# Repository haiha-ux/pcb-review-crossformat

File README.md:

# Reviewing Altium / Eagle (and other) PCB designs in KiCad: how faithful is the import?

Clients send board files from Altium, Eagle, EasyEDA or Allegro. Before reviewing such a file in KiCad 10, I want
to know what the import keeps and what it silently changes. This repo measures that on two public boards, then (next
milestone) reviews each one the way a client would get it.

**Status:** milestone 1 (import fidelity) done; milestone 2 adds one sample review report per board
(`review/*/REVIEW.md`).

## The two sample boards

| | Altium | Eagle |
|---|---|---|
| Board | Bluetooth audio receiver (JieLi IC), 50 × 43 mm, 2 layers | SparkFun Qwiic Button, 25.4 × 25.4 mm, 2 layers, and its 3 × 3 production panel |
| Source | github.com/LZH-ang/Bluetooth-Audio-with-JieLi-IC, `PCB_Project/` | github.com/sparkfun/Qwiic_Button, `Hardware/`, `Production/` |
| License | GPL-3.0 (`samples/altium_blv/original/LICENSE`) | CC BY-SA 4.0 (`samples/eagle_qwiic_button/original/LICENSE.md`) |
| Design file | `BLV.PcbDoc` (native binary, OLE), `BLV.SchDoc` | `Qwiic_Button.brd` / `.sch` (Eagle 9.5.2 XML), `Qwiic_Button-Panel.brd` |
| Maker's Gerbers | `BLV.GTL/GBL/GTS/GBS/GTO/GBO/GKO`, NC drill, drill report | `Qwiic_Button-Panel.GTL/…/GKO`, Excellon `.TXT` |

The sample files are copied unchanged under `samples/*/original/`, with their licenses. Everything else in this
repo is my own work.

I chose a native binary PcbDoc on purpose. Many "Altium" files on GitHub are the ASCII variant exported by EasyEDA
(they start with `|RECORD=`), and those exercise a different reader.

## Method

1. **Import:** `kicad-cli pcb import --format altium|eagle` (KiCad 10.0.8), saved with its JSON import report
   (`samples/*/kicad/import_report*.json`).
2. **"Before" numbers from the original file, without KiCad** (`tools/source_metrics.py`).
   - PcbDoc: each `<Name>6/Header` stream holds the record count of `<Name>6/Data`. `Tracks6` is decoded record by
     record, with the layout from KiCad's `altium_parser_pcb.cpp`, so free copper tracks can be told apart from
     polygon and footprint primitives.
   - Eagle: the XML is read directly.
   - Rules: read from the PcbDoc `Rules6` stream and the Eagle `<designrules>`.
3. **"After" numbers from KiCad** (`tools/kicad_metrics.py`, pcbnew).
4. **Copper check against the maker's Gerbers** (`tools/reexport.py`, `tools/gerber_xor.py`).
   - The design is loaded through KiCad's importer, zones are refilled, and Gerbers and drill files are written.
   - Each layer is then drawn by gerbonara (an independent Gerber reader), rasterised at 0.05 mm/pixel and XORed
     against the maker's Gerber.
   - The two sets are registered on the top copper by phase correlation, because they do not share an origin and
     their outline layers differ.
   - Differences thinner than about 0.15 mm (3 pixels) are treated as rasterisation noise.
   - Tool check: the same file against itself gives 0.000 mm². F.Cu against B.Cu of one board gives 52 / 194 mm².

## Fidelity: Altium `BLV.PcbDoc`

| Item | Original (PcbDoc) | After KiCad import | Verdict |
|---|---|---|---|
| Components / footprints | 33 | 36 | The 3 extras are the free pads of the three 3.048 mm holes, wrapped in unnamed footprints |
| Nets | 31 | 31 | same |
| Pads | 109 | 110 (97 SMD, 13 PTH) | +1 is the printed antenna of A3: copper inside the footprint that carries a net, which KiCad can only keep as a pad, so it becomes a 17.5 × 6.35 mm custom-shape pad next to the real feed pad |
| Vias | 102 | 102 | same |
| Free copper tracks (straight, `Tracks6`) | 81 | 81 | same |
| Free copper arcs (`Arcs6`) | 51 | 50 | the missing arc is 0.0002 mm long (a 0.012° sweep at net 25); KiCad drops it as degenerate |
| Straight track length, top / bottom | 118.99 / 59.56 mm | 118.99 / 59.56 mm | identical to 0.01 mm |
| Arc length, top / bottom | 48.78 / 10.50 mm | 48.78 / 10.50 mm | identical |
| **All free copper (tracks + arcs), top / bottom** | **167.77 / 70.06 mm** | **167.77 / 70.06 mm** | identical |
| Polygons | 6 | 6 zones | same; each keeps its 10 mil gap |
| Keep-out tracks | 3 | 3 rule areas | kept as keep-outs |
| Drill hits | 115 (BLV.DRR) | 115 | same |
| Clearance rule | 10 mil | 0.2 mm default (7.9 mil) | **lost** |
| Track width rule | min 10 mil, preferred 12 mil | 0.2 mm default | **lost** |
| Hole-to-hole rule | 10 mil | not set | **lost** |
| Polygon connect (Rules6) | SMD pads and vias: Direct; TH pads: relief 12 mil | every pad: thermal relief 0.254 mm | **changed** |
| Solder mask expansion | 4 mil (BLV.RUL) | 0 | **lost** |

Copper XOR against the maker's Gerbers:

| Layer | Maker mm² | KiCad mm² | Only in maker's | Only in KiCad's | What it is |
|---|---|---|---|---|---|
| Top copper | 742.9 | 714.3 | 23.9 | 1.1 | rings around SMD GND pads and vias: Altium connects them Direct, KiCad refills with thermal reliefs |
| Bottom copper | 797.9 | 786.1 | 6.1 | 0.8 | same cause |
| Top mask | 222.2 | 175.6 | 18.8 | 0.3 | mask openings lack the 4 mil expansion |
| Bottom mask | 83.0 | 67.4 | 3.1 | 0.3 | same |
| Top / bottom silk | 128.2 / 24.3 | 117.6 / 19.8 | 19.6 / 9.1 | 3.6 / 3.1 | text drawn in a different font |

No track, pad or via copper is missing. Every copper difference is a polygon-to-pad connection (diff image
`results/xor_blv/diff_F_Cu.png`). Before signing off a review on the imported board, re-enter the clearance,
width, mask and polygon-connect rules by hand, or refill the zones with the original style. Otherwise a DRC in
KiCad checks against looser rules than the designer used.

## Fidelity: Eagle `Qwiic_Button.brd` (and the production panel)

| Item | Original (.brd XML) | After KiCad import | Verdict |
|---|---|---|---|
| Elements / footprints | 48 | 48 (22 without pads: logos, frame, fiducial marks) | same |
| Signals / nets | 21 | 21 | same |
| Vias | 38 | 38 | same |
| Wires / tracks | 193 | 193 | same |
| Wire length, top / bottom | 214.12 / 79.95 mm | 214.12 / 79.95 mm | identical |
| Polygons | 2 | 2 zones | same |
| Copper clearance (mdWireWire) | 7 mil | min clearance 0.1778 mm (7 mil) | kept |
| Minimum width (msWidth) | 7 mil | min track 0.2 mm | **changed** (stricter than the design) |
| tRestrict / bRestrict arcs (STAND-OFF) | 8 | on an undefined layer | **lost**: no copper keep-out around the screw holes |
| Dimension lines + "Units in Inches" text | 3 | on an undefined layer | lost (documentation only) |
| Panel V-score lines and labels (`Qwiic_Button-Panel.GKO`) | present | not in Edge.Cuts | **lost**: the panel cannot be re-fabbed from the KiCad export |
| Drill hits, panel | 423 | 36 NPTH + 387 PTH = 423 | same |

Track length counts only routed copper ("free" primitives: not part of a footprint, a polygon or a keep-out). On
both boards it is the sum of straight segments and arcs, so the Altium straight-only row and the all-segments row
are both shown.

- **Practical catch:** the `.kicad_pcb` written by `kicad-cli pcb import` contains items on the UNDEFINED layer.
  KiCad then refuses to reopen that file ("One or more items were found on undefined layers"), both from
  `kicad-cli` and from the pcbnew API.
  - In the GUI, the importer asks for a layer mapping, so mapping Eagle layers 41/42 to a rule area or a user layer
    there avoids the problem.
  - The scripts here load the `.brd` through KiCad's Eagle plugin in memory and move those items to Cmts.User
    (11 on the single board, 88 on the panel), listing them.

Copper XOR, production panel (3 × 3):

| Layer | Maker mm² | KiCad mm² | Only in maker's | Only in KiCad's | What it is |
|---|---|---|---|---|---|
| Top copper | 3794.0 | 4060.3 | 137.0 | 388.1 | Eagle `<hole>`s become NPTH pads larger than the drill (3.302 mm stand-off holes as 3.607 mm pads, the 1.6 mm pegs of the 12 mm switch as 1.905 mm pads) and KiCad plots their copper; the pour also runs into the STAND-OFF restrict circles; the red frame is the pour pulled back 0.5 mm from the edge instead of 7 mil |
| Bottom copper | 4446.7 | 4488.4 | 220.0 | 255.4 | same causes |
| Top / bottom mask | 1232.8 / 700.2 | 1246.6 / 716.2 | 0.0 / 0.0 | 0.0 / 0.0 | match |
| Top / bottom silk | 415.2 / 814.9 | 457.8 / 828.1 | 0.0 / 0.0 | 4.0 / 2.0 | match, KiCad strokes slightly wider |
| Outline | 632.8 | 326.3 | 299.6 | 0 | V-score lines and labels missing |

Most of the NPTH copper is drilled away, but a ring of 0.15 mm stays around each hole, and a fab's CAM check may
flag copper on an unplated hole. The restrict loss matters: the pour runs under the screw heads of the stand-offs.

### The corrected Eagle board

`tools/reexport.py --fix-eagle` loads the `.brd` the same way and then puts back, by hand, what the import lost:

1. a copper keep-out disc (fills, tracks, vias; both layers) of radius 1.956 mm on every STAND-OFF, which is the
   outer edge of Eagle's 0.2032 mm restrict ring at r = 1.854 mm;
2. NPTH pads without copper (the mask openings are kept);
3. copper-to-edge 7 mil (Eagle `mdCopperDimension`; the import left KiCad's 0.5 mm);
4. on the panel, the 8 V-score lines moved to `User.1` with a keep-out strip of the same 7 mil pull-back. This made
   no measurable copper difference, because the lines run in the gaps between boards.

The corrected boards open in KiCad (the script reloads each one before writing fab files):
`samples/eagle_qwiic_button/kicad/fixed/Qwiic_Button_fixed.kicad_pcb` and
`samples/eagle_qwiic_button/kicad/fixed_panel/Qwiic_Button-Panel_fixed.kicad_pcb`.

XOR of the corrected panel against the maker's Gerbers (`results/xor_qwiic_panel_fixed/`):

| Layer | Only in maker's, import as is → corrected | Only in KiCad's, import as is → corrected |
|---|---|---|
| Top copper | 137.0 → **0.0** mm² | 388.1 → 247.5 mm² |
| Bottom copper | 220.0 → 10.2 mm² | 255.4 → 162.7 mm² |
| Masks, silk | unchanged (match) | unchanged |

The stand-off discs, the NPTH rings and the edge frame are gone. What KiCad still pours and Eagle did not is the
same three spots on each of the nine boards: the corner between the H2 hole and the left edge, a small island
inside a track loop between S1 and U4, and a thin ring just outside the H1 keep-out. All three are GND pour that Eagle's
fill engine left out and KiCad's keeps, which points at the two engines treating isolated or narrow regions
differently (Eagle removes unconnected polygon parts, "orphans"). I tried raising KiCad's minimum fill width to
Eagle's 0.2032 mm polygon width: the difference grew (top copper only-KiCad 446 mm²), so that is not the cause, and
the rest is left as an unexplained pour difference. The panel outline difference stays: V-score is not a cut, so
it is not put on Edge.Cuts.

## What to ask a client for

| Tool | Send | Why |
|---|---|---|
| Altium Designer | `.PcbDoc` + `.SchDoc` + `.PrjPcb`, **and** the Gerber/NC drill set and `*.RUL` / design-rule report of the same revision | geometry imports cleanly, rules do not (see above); the rule report and Gerbers are the reference |
| Eagle / Fusion Electronics | `.brd` + `.sch` (XML, Eagle 6+), the `.dru` rules file, and the CAM output | restrict layers and panel milling/V-score layers need checking against the CAM output |
| EasyEDA / EasyEDA Pro | the project export (JSON / `.epro`) plus Gerbers | KiCad 10 has EasyEDA and EasyEDA Pro importers (in pcbnew's plugin list); not measured here yet |
| Cadence Allegro | the `.brd`, or better a FabMaster extract, ODB++ or IPC-2581, plus Gerbers | KiCad 10 lists Allegro, FabMaster, ODB++ and IPC-2581 importers; no openly licensed Allegro sample was found for this study |
| Any tool | Gerbers + drill of the exact revision | the only ground truth that does not depend on any importer |

## Files

| Path | What |
|---|---|
| `samples/*/original/` | the public design files and the maker's Gerbers, unchanged, with their licenses |
| `samples/*/kicad/` | KiCad import (`.kicad_pcb`), import report, re-exported Gerbers; `fixed*/` the corrected Eagle boards |
| `review/*/REVIEW.md` | the two sample review reports, with crop images in `img/` and the DRC JSON they are based on |
| `results/*_source.json`, `results/*_kicad.json` | counts before / after |
| `results/xor_*/` | per-layer XOR report and diff images (red = only in the maker's Gerber, blue = only in KiCad's) |
| `tools/` | the scripts above; `gerber_xor.py` needs gerbonara (path in `GERBONARA_PY`) and CairoSVG; `review_board.py` restores the original rules and runs DRC; `crops.py` renders the report images |

## License

- The sample designs and the maker's Gerbers under `samples/*/original/` keep their own licenses: GPL-3.0 for the
  Altium board (`samples/altium_blv/original/LICENSE`), CC BY-SA 4.0 for the SparkFun board
  (`samples/eagle_qwiic_button/original/LICENSE.md`).
- Files derived from a sample keep that sample's license: the KiCad imports and corrected boards, re-exported
  Gerbers, diff images and the review report with its images under `review/<sample>/`.
- My own scripts in `tools/` and the text of this README are MIT licensed (`LICENSE`).

## Not checked yet

- Schematic import: `kicad-cli` only imports boards; schematics go through the KiCad GUI importers.
- Allegro and EasyEDA samples.

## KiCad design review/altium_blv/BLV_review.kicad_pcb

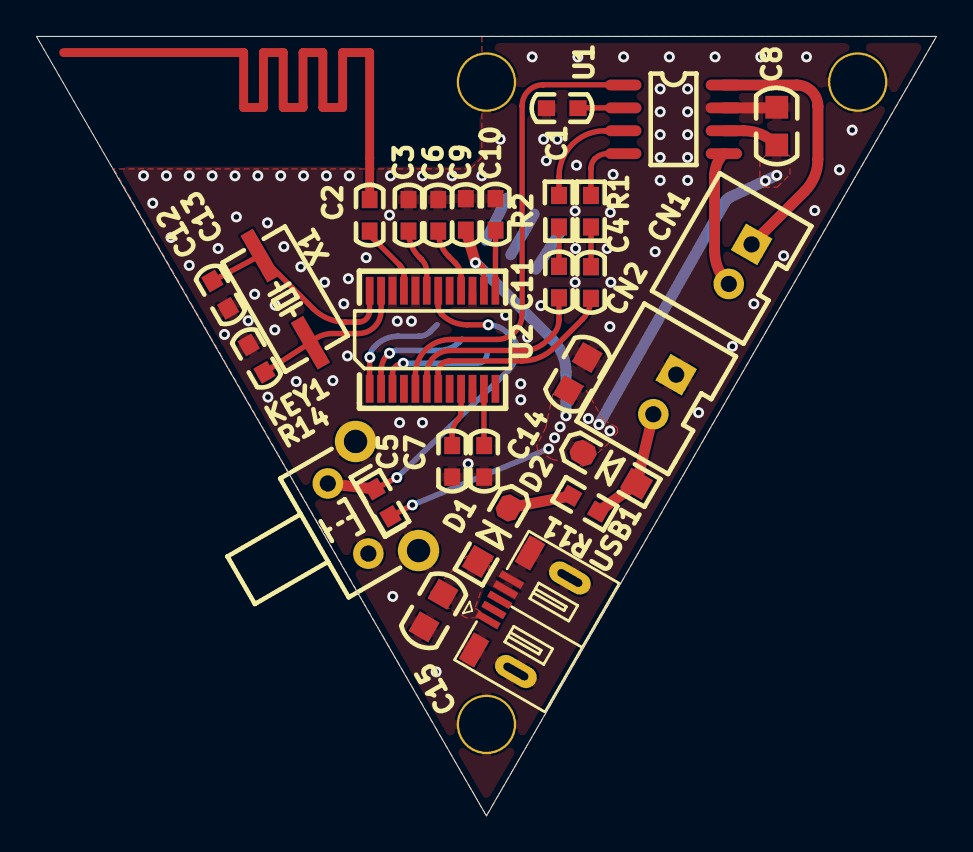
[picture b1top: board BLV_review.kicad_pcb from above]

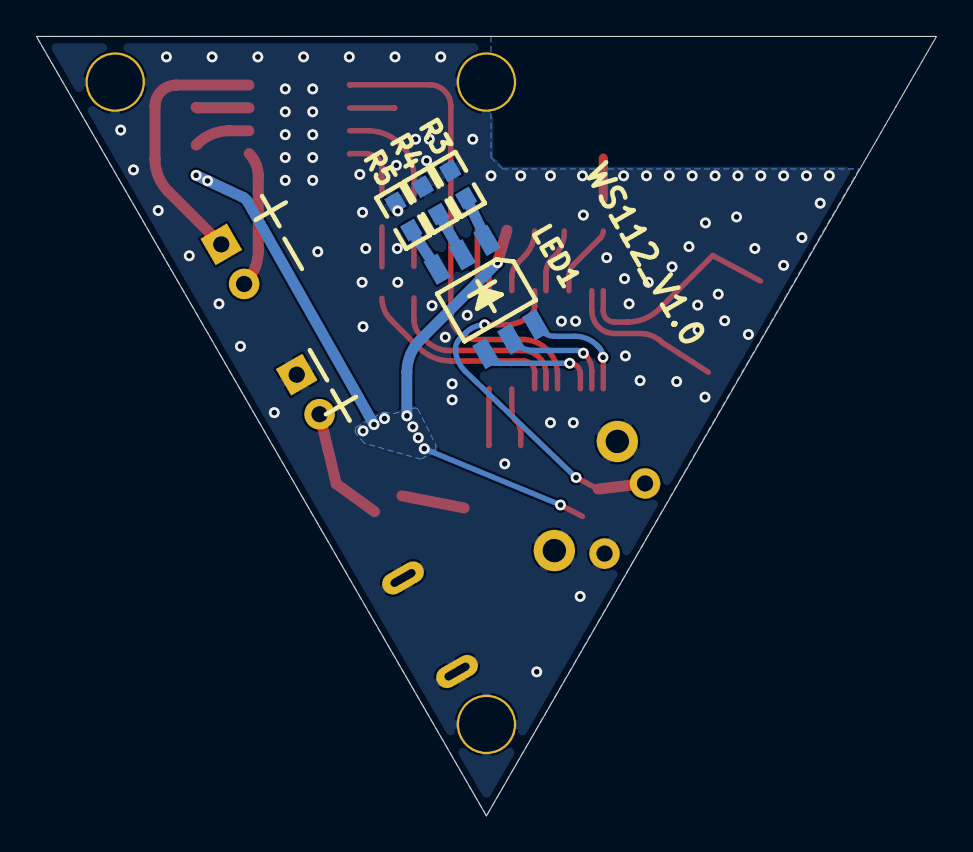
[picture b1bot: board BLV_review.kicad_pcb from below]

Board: 2 copper layers, 50.0 x 43.3 mm, 33 parts (4 on the bottom side), 31 nets.

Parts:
A3: 2.4G天线; ANT-RF-BT6-2.4G
C1, C3, C5, C6: 1u; C0603
C2, C12, C13: 10p; C0603
C4, C11: 10n; C0603
C7: 560n; C0603
C8, C15: 10u; C0805
C9, C10: 10u; C0603
C14: 100n; C0805
CN1, CN2: XH2.54; XH2.54-LI-2P
D1: T4; SOD-123
D2: S4; SOD-123
KEY1: DIP 6*6*8; TSW DIP-6*6*8
LED1: RGB; LED 5050
R1, R2, R14: 47k; R0603
R3, R4, R5: 5k1; R0603
R11: 150; R0603
U1: ANT8110S; SOP8
U2: AS1711-5C4; QSOP24
USB1: U254-051T-4BH82-S2S; USB-MICRO_B
X1: 24MHz; 49XSMD

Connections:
3.3V: C8.1, C9.2, C14.2, D2.1, R14.2, U1.6, U2.14
GND: C1.2, C3.2, C5.1, C6.2, C7.1, C8.2, C9.1, C10.2, C12.2, C13.2, C14.1, C15.2, CN2.1, KEY1.2, KEY1.3, KEY1.4, R3.1, R4.1, R5.1, U1.7, U2.10, U2.15, U2.20, U2.22, USB1.4, USB1.5, USB1.6, USB1.7, USB1.8, USB1.9
NetA3_1: A3.1, C2.2
NetC1_1: C1.1, U1.2
NetC2_1: C2.1, U2.21
NetC3_1: C3.1, U2.19
NetC4_1: C4.1, U2.7
NetC4_2: C4.2, R1.2
NetC5_2: C5.2, U2.9
NetC6_1: C6.1, U2.16
NetC7_2: C7.2, U2.11
NetC10_1: C10.1, U2.13
NetC11_1: C11.1, U2.6
NetC11_2: C11.2, R2.2
NetC12_1: C12.1, U2.23, X1.2
NetC13_1: C13.1, U2.24, X1.1
NetCN1_1: CN1.1, U1.8
NetCN1_2: CN1.2, U1.5
NetCN2_2: CN2.2, D2.2, R11.1
NetD1_1: D1.1, R11.2
NetKEY1_1: KEY1.1, R14.1, U2.18
NetLED1_1: LED1.1, R5.2
NetLED1_2: LED1.2, R4.2
NetLED1_3: LED1.3, R3.2
NetLED1_4: LED1.4, U2.1
NetLED1_5: LED1.5, U2.2
NetLED1_6: LED1.6, U2.3
NetR1_1: R1.1, U1.4
NetR2_1: R2.1, U1.3
NetU1_1: U1.1, U2.5
VIN: C15.1, D1.2, USB1.1

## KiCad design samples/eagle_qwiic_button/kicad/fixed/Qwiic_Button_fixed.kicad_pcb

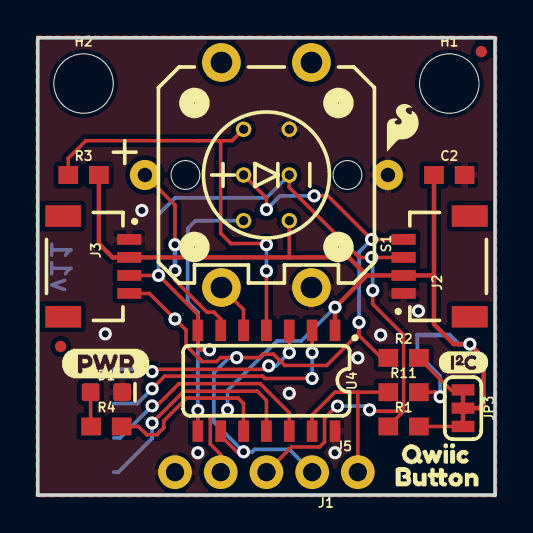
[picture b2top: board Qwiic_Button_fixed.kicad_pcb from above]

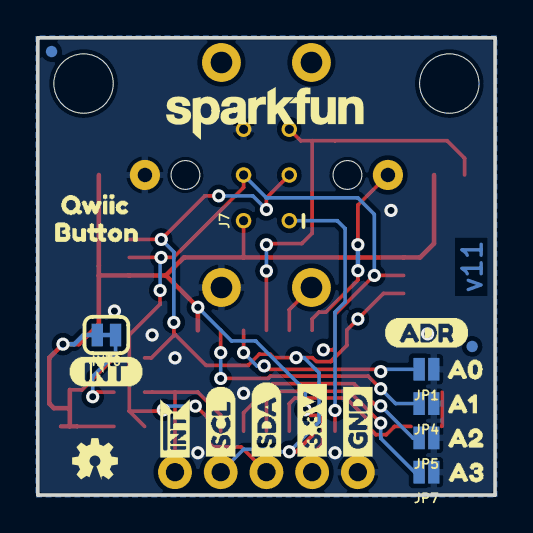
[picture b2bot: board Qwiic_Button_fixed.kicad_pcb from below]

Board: 2 copper layers, 25.4 x 25.4 mm, 48 parts (23 on the bottom side), 18 nets.

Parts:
C2: 0.1uF; 0603
D1: RED; LED-0603
FRAME1: FRAME-LETTER; CREATIVE_COMMONS
H1, H2: STAND-OFF
INT0: JUMPER-SMT_2_NC_TRACE_SILK; SMT-JUMPER_2_NC_TRACE_SILK
J1: 1X04_NO_SILK
J2, J3: QWIIC_RIGHT_ANGLE; JST04_1MM_RA
J5: 1X01_NO_SILK
J7: ISP; 2X3_TEST_POINTS
JP1, JP4, JP5, JP7: JUMPER-SMT_2_NO_NO-SILK; SMT-JUMPER_2_NO_NO-SILK
JP2, JP6, JP8, JP9: FIDUCIALUFIDUCIAL; MICRO-FIDUCIAL
JP3: JUMPER-SMT_3_2-NC_TRACE_SILK; SMT-JUMPER_3_2-NC_TRACE_SILK
LOGO1: OSHW-LOGOMINI; OSHW-LOGO-MINI
LOGO2: REVISION
LOGO3: SFE_LOGO_NAME.1_INCH; SFE_LOGO_NAME_.1
LOGO4: SFE_LOGO_FLAME.1_INCH; SFE_LOGO_FLAME_.1
R1, R2: 2.2k; 0603
R3, R11: 10k; 0603
R4: 1k; 0603
S1: Button; TACTILE_SWITCH_LED_PTH_12MM
U4: ATTINY84-ARDUINO; SO14
U$1, U$2: BUTTON1
U$3: PWR-()-04
U$4: INT-()-04
U$5: SCL
U$6: SDA
U$7: 3.3V
U$8: GND
U$9: (ADR)
U$10: I_SUPER2_C-()-03
U$15: INT#-[_-04
U$16: A00
U$17: A11
U$19: A22
U$20, U$23: QWIIC0
U$21: A33

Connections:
3.3V: C2.1, INT0.2, J1.3, J2.2, J3.2, J7.2, JP3.2, R3.2, U4.1
ADR0: JP1.2, U4.3
ADR1: JP4.2, U4.2
ADR2: JP5.2, U4.12
ADR3: JP7.2, U4.11
GND: C2.2, D1.C, J1.4, J2.1, J3.1, J7.6, JP1.1, JP4.1, JP5.1, JP7.1, S1.2, S1.C, U4.14
INT_R: INT0.1, R11.2
LED: S1.A, U4.6
MISO: J7.1, U4.8
unnamed: D1.A, R4.1
SCL: J1.1, J2.4, J3.4, J7.3, R2.1, U4.9
SCL_PU1: JP3.1, R2.2
SDA: J1.2, J2.3, J3.3, J7.4, R1.1, U4.7
SDA_PU1: JP3.3, R1.2
STAT: R4.2, U4.10
SWITCH: S1.4, U4.5
~INT: J5.1, R11.1, U4.13
~RST: J7.5, R3.1, U4.4

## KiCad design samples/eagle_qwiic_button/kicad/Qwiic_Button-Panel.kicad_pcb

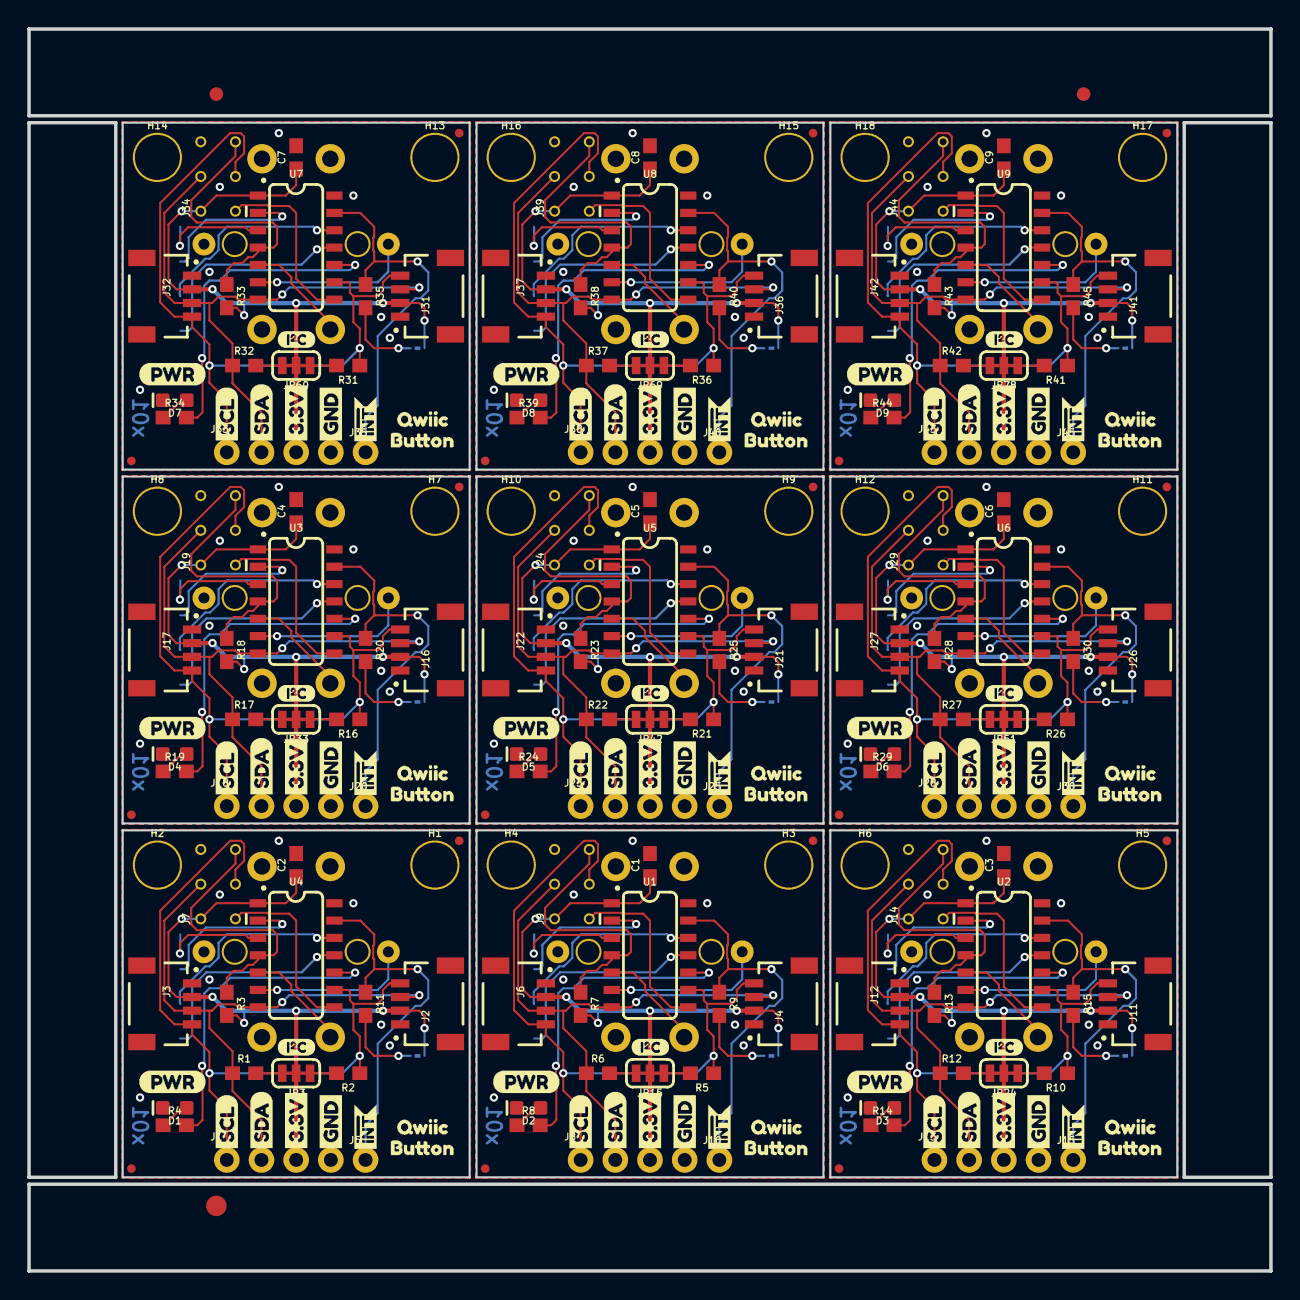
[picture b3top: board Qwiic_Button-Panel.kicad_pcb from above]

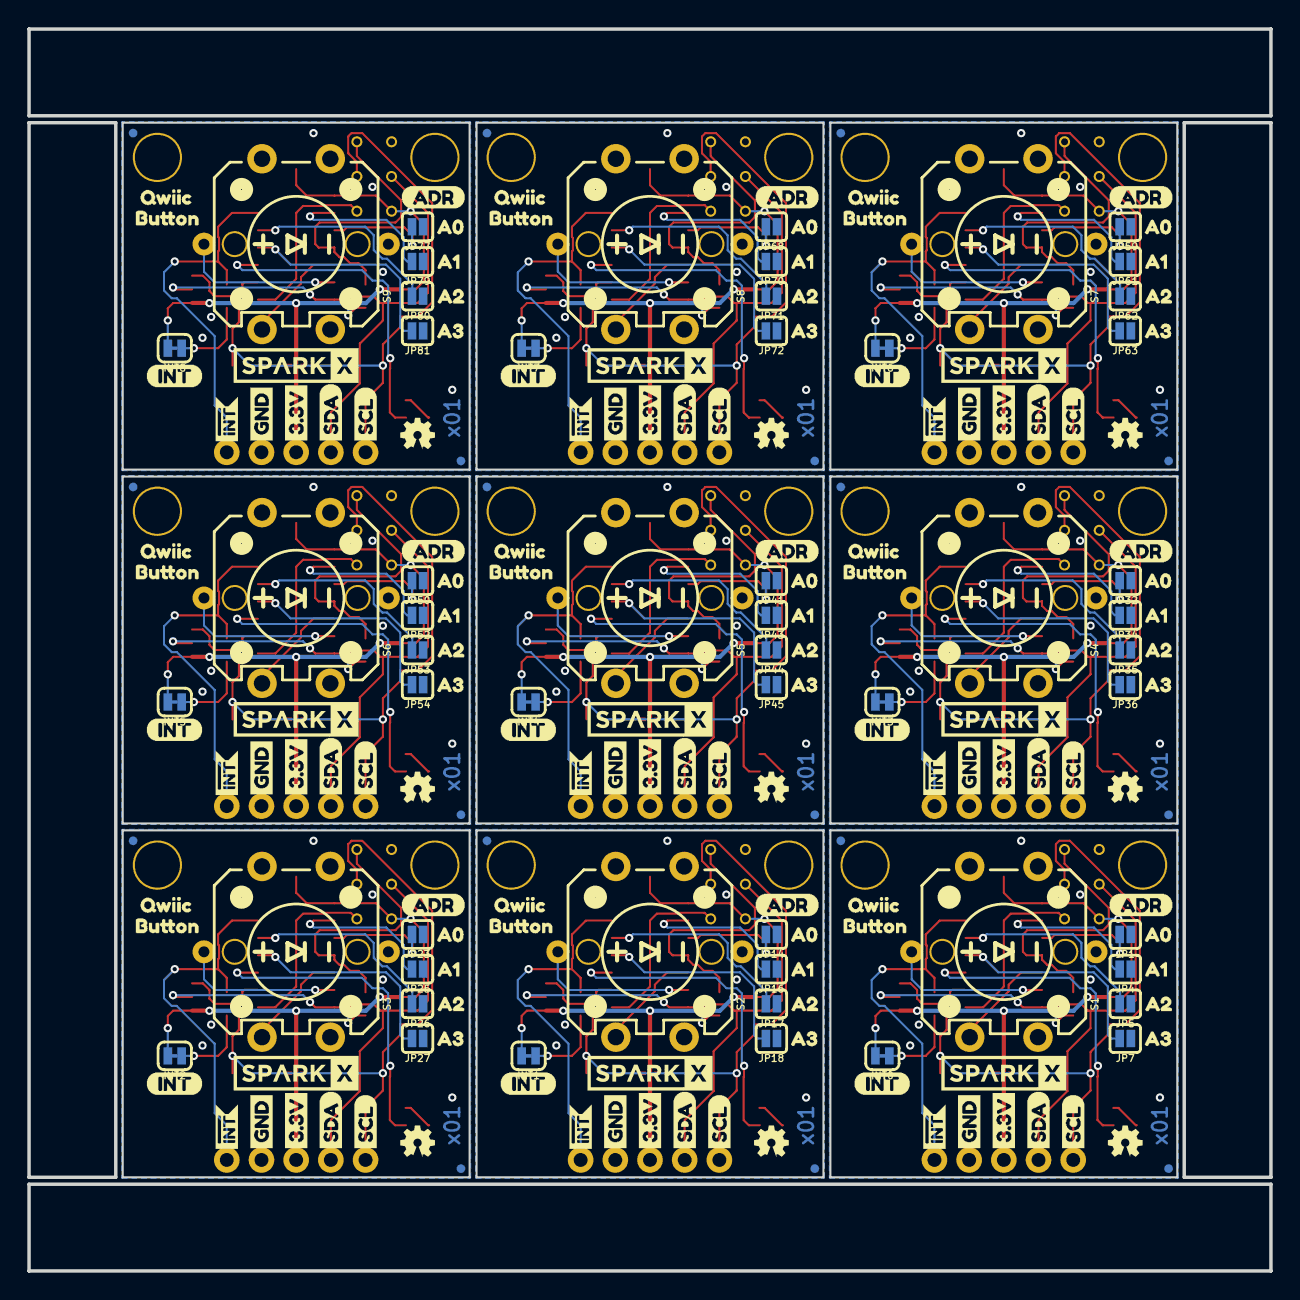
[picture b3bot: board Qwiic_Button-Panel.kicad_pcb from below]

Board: 2 copper layers, 90.9 x 90.9 mm, 453 parts (207 on the bottom side), 162 nets.

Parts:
C1, C2, C3, C4, C5, C6, C7, C8, C9: 0.1uF; 0603
D1, D2, D3, D4, D5, D6, D7, D8, D9: RED; LED-0603
E$1, E$2: FIDUCIAL-1X2
E$3: FIDUCIAL-1.5X3
H1, H2, H3, H4, H5, H6, H7, H8, H9, H10, H11, H12, H13, H14, H15, H16, H17, H18: STAND-OFF
INT0, INT1, INT2, INT3, INT4, INT5, INT6, INT7, INT8: SMT-JUMPER_2_NC_TRACE_SILK
J1, J8, J13, J18, J23, J28, J33, J38, J43: 1X04_NO_SILK
J2, J3, J4, J6, J11, J12, J16, J17, J21, J22, J26, J27, J31, J32, J36, J37, J41, J42: JST04_1MM_RA
J5, J10, J15, J20, J25, J30, J35, J40, J45: 1X01_NO_SILK
J7, J9, J14, J19, J24, J29, J34, J39, J44: ISP; 2X3_TEST_POINTS
JP1, JP4, JP5, JP7, JP14, JP16, JP17, JP18, JP23, JP25, JP26, JP27, JP32, JP34, JP35, JP36, JP41, JP43, JP44, JP45, JP50, JP52, JP53, JP54, JP59, JP61, JP62, JP63, JP68, JP70, JP71, JP72, JP77, JP79, JP80, JP81: SMT-JUMPER_2_NO_SILK
JP2, JP6, JP8, JP9, JP10, JP11, JP12, JP13, JP19, JP20, JP21, JP22, JP28, JP29, JP30, JP31, JP37, JP38, JP39, JP40, JP46, JP47, JP48, JP49, JP55, JP56, JP57, JP58, JP64, JP65, JP66, JP67, JP73, JP74, JP75, JP76: FIDUCIALUFIDUCIAL; MICRO-FIDUCIAL
JP3, JP15, JP24, JP33, JP42, JP51, JP60, JP69, JP78: SMT-JUMPER_3_2-NC_TRACE_SILK
LOGO1, LOGO2, LOGO3, LOGO4, LOGO5, LOGO6, LOGO7, LOGO8, LOGO9: OSHW-LOGOMINI; OSHW-LOGO-MINI
R1, R2, R5, R6, R10, R12, R16, R17, R21, R22, R26, R27, R31, R32, R36, R37, R41, R42: 2.2k; 0603
R3, R7, R9, R11, R13, R15, R18, R20, R23, R25, R28, R30, R33, R35, R38, R40, R43, R45: 10k; 0603
R4, R8, R14, R19, R24, R29, R34, R39, R44: 1k; 0603
S1, S2, S3, S4, S5, S6, S7, S8, S9: Button; TACTILE_SWITCH_LED_PTH_12MM
U1, U2, U3, U4, U5, U6, U7, U8, U9: ATTINY84-ARDUINO; SO14
U$1, U$2, U$38, U$39, U$61, U$62, U$84, U$85, U$107, U$108, U$130, U$131, U$153, U$154, U$176, U$177, U$199, U$200: BUTTON1
U$3, U$42, U$65, U$88, U$111, U$134, U$157, U$180, U$203: PWR-()-04
U$4, U$37, U$60, U$83, U$106, U$129, U$152, U$175, U$198: INT-()-04
U$5, U$14, U$24, U$34, U$47, U$57, U$70, U$80, U$93, U$103, U$116, U$126, U$139, U$149, U$162, U$172, U$185, U$195: SCL
U$6, U$12, U$25, U$33, U$48, U$56, U$71, U$79, U$94, U$102, U$117, U$125, U$140, U$148, U$163, U$171, U$186, U$194: SDA
U$7, U$22, U$26, U$30, U$49, U$53, U$72, U$76, U$95, U$99, U$118, U$122, U$141, U$145, U$164, U$168, U$187, U$191: 3.3V
U$8, U$13, U$27, U$29, U$50, U$52, U$73, U$75, U$96, U$98, U$119, U$121, U$142, U$144, U$165, U$167, U$188, U$190: GND
U$9, U$28, U$51, U$74, U$97, U$120, U$143, U$166, U$189: (ADR)
U$10, U$31, U$54, U$77, U$100, U$123, U$146, U$169, U$192: I_SUPER2_C-()-03
U$11, U$15, U$32, U$35, U$55, U$58, U$78, U$81, U$101, U$104, U$124, U$127, U$147, U$150, U$170, U$173, U$193, U$196: INT#-[_-04
U$16, U$43, U$66, U$89, U$112, U$135, U$158, U$181, U$204: A00
U$17, U$44, U$67, U$90, U$113, U$136, U$159, U$182, U$205: A11
U$18, U$36, U$59, U$82, U$105, U$128, U$151, U$174, U$197: SPARKX-MEDIUM
U$19, U$45, U$68, U$91, U$114, U$137, U$160, U$183, U$206: A22
U$20, U$23, U$40, U$41, U$63, U$64, U$86, U$87, U$109, U$110, U$132, U$133, U$155, U$156, U$178, U$179, U$201, U$202: QWIIC0
U$21, U$46, U$69, U$92, U$115, U$138, U$161, U$184, U$207: A33

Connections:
3.3V: C2.1, INT0.2, J1.3, J2.2, J3.2, J7.2, JP3.2, R3.2, U4.1
3.3V1: C1.1, INT1.2, J4.2, J6.2, J8.3, J9.2, JP15.2, R7.2, U1.1
3.3V2: C3.1, INT2.2, J11.2, J12.2, J13.3, J14.2, JP24.2, R13.2, U2.1
3.3V3: C4.1, INT3.2, J16.2, J17.2, J18.3, J19.2, JP33.2, R18.2, U3.1
3.3V4: C5.1, INT4.2, J21.2, J22.2, J23.3, J24.2, JP42.2, R23.2, U5.1
3.3V5: C6.1, INT5.2, J26.2, J27.2, J28.3, J29.2, JP51.2, R28.2, U6.1
3.3V6: C7.1, INT6.2, J31.2, J32.2, J33.3, J34.2, JP60.2, R33.2, U7.1
3.3V7: C8.1, INT7.2, J36.2, J37.2, J38.3, J39.2, JP69.2, R38.2, U8.1
3.3V8: C9.1, INT8.2, J41.2, J42.2, J43.3, J44.2, JP78.2, R43.2, U9.1
ADR0: JP1.2, U4.3
ADR1: JP4.2, U4.2
ADR2: JP5.2, U4.12
ADR3: JP7.2, U4.11
ADR4: JP14.2, U1.3
ADR5: JP16.2, U1.2
ADR6: JP17.2, U1.12
ADR7: JP18.2, U1.11
ADR8: JP23.2, U2.3
ADR9: JP25.2, U2.2
ADR10: JP26.2, U2.12
ADR11: JP27.2, U2.11
ADR12: JP32.2, U3.3
ADR13: JP34.2, U3.2
ADR14: JP35.2, U3.12
ADR15: JP36.2, U3.11
ADR16: JP41.2, U5.3
ADR17: JP43.2, U5.2
ADR18: JP44.2, U5.12
ADR19: JP45.2, U5.11
ADR20: JP50.2, U6.3
ADR21: JP52.2, U6.2
ADR22: JP53.2, U6.12
ADR23: JP54.2, U6.11
ADR24: JP59.2, U7.3
ADR25: JP61.2, U7.2
ADR26: JP62.2, U7.12
ADR27: JP63.2, U7.11
ADR28: JP68.2, U8.3
ADR29: JP70.2, U8.2
ADR30: JP71.2, U8.12
ADR31: JP72.2, U8.11
ADR32: JP77.2, U9.3
ADR33: JP79.2, U9.2
ADR34: JP80.2, U9.12
ADR35: JP81.2, U9.11
GND: C2.2, D1.C, J1.4, J2.1, J3.1, J7.6, JP1.1, JP4.1, JP5.1, JP7.1, S1.2, S1.C, U4.14
GND1: C1.2, D2.C, J4.1, J6.1, J8.4, J9.6, JP14.1, JP16.1, JP17.1, JP18.1, S2.2, S2.C, U1.14
GND2: C3.2, D3.C, J11.1, J12.1, J13.4, J14.6, JP23.1, JP25.1, JP26.1, JP27.1, S3.2, S3.C, U2.14
GND3: C4.2, D4.C, J16.1, J17.1, J18.4, J19.6, JP32.1, JP34.1, JP35.1, JP36.1, S4.2, S4.C, U3.14
GND4: C5.2, D5.C, J21.1, J22.1, J23.4, J24.6, JP41.1, JP43.1, JP44.1, JP45.1, S5.2, S5.C, U5.14
GND5: C6.2, D6.C, J26.1, J27.1, J28.4, J29.6, JP50.1, JP52.1, JP53.1, JP54.1, S6.2, S6.C, U6.14
GND6: C7.2, D7.C, J31.1, J32.1, J33.4, J34.6, JP59.1, JP61.1, JP62.1, JP63.1, S7.2, S7.C, U7.14
GND7: C8.2, D8.C, J36.1, J37.1, J38.4, J39.6, JP68.1, JP70.1, JP71.1, JP72.1, S8.2, S8.C, U8.14
GND8: C9.2, D9.C, J41.1, J42.1, J43.4, J44.6, JP77.1, JP79.1, JP80.1, JP81.1, S9.2, S9.C, U9.14
INT_R: INT0.1, R11.2
INT_R1: INT1.1, R9.2
INT_R2: INT2.1, R15.2
INT_R3: INT3.1, R20.2
INT_R4: INT4.1, R25.2
INT_R5: INT5.1, R30.2
INT_R6: INT6.1, R35.2
INT_R7: INT7.1, R40.2
INT_R8: INT8.1, R45.2
LED: S1.A, U4.6
LED1: S2.A, U1.6
LED2: S3.A, U2.6
LED3: S4.A, U3.6
LED4: S5.A, U5.6
LED5: S6.A, U6.6
LED6: S7.A, U7.6
LED7: S8.A, U8.6
LED8: S9.A, U9.6
MISO: J7.1, U4.8
MISO1: J9.1, U1.8
MISO2: J14.1, U2.8
MISO3: J19.1, U3.8
MISO4: J24.1, U5.8
MISO5: J29.1, U6.8
MISO6: J34.1, U7.8
MISO7: J39.1, U8.8
MISO8: J44.1, U9.8
unnamed: D2.A, R8.1
unnamed: D3.A, R14.1
unnamed: D1.A, R4.1
unnamed: D4.A, R19.1
unnamed: D5.A, R24.1
unnamed: D6.A, R29.1
unnamed: D7.A, R34.1
unnamed: D8.A, R39.1
unnamed: D9.A, R44.1
SCL: J1.1, J2.4, J3.4, J7.3, R2.1, U4.9
SCL1: J4.4, J6.4, J8.1, J9.3, R5.1, U1.9
SCL2: J11.4, J12.4, J13.1, J14.3, R10.1, U2.9
SCL3: J16.4, J17.4, J18.1, J19.3, R16.1, U3.9
SCL4: J21.4, J22.4, J23.1, J24.3, R21.1, U5.9
SCL5: J26.4, J27.4, J28.1, J29.3, R26.1, U6.9
SCL6: J31.4, J32.4, J33.1, J34.3, R31.1, U7.9
SCL7: J36.4, J37.4, J38.1, J39.3, R36.1, U8.9
SCL8: J41.4, J42.4, J43.1, J44.3, R41.1, U9.9
SCL_PU1: JP3.1, R2.2
SCL_PU2: JP15.1, R5.2
SCL_PU3: JP24.1, R10.2
SCL_PU4: JP33.1, R16.2
SCL_PU5: JP42.1, R21.2
SCL_PU6: JP51.1, R26.2
SCL_PU7: JP60.1, R31.2
SCL_PU8: JP69.1, R36.2
SCL_PU9: JP78.1, R41.2
SDA: J1.2, J2.3, J3.3, J7.4, R1.1, U4.7
SDA1: J4.3, J6.3, J8.2, J9.4, R6.1, U1.7
SDA2: J11.3, J12.3, J13.2, J14.4, R12.1, U2.7
SDA3: J16.3, J17.3, J18.2, J19.4, R17.1, U3.7
SDA4: J21.3, J22.3, J23.2, J24.4, R22.1, U5.7
SDA5: J26.3, J27.3, J28.2, J29.4, R27.1, U6.7
SDA6: J31.3, J32.3, J33.2, J34.4, R32.1, U7.7
SDA7: J36.3, J37.3, J38.2, J39.4, R37.1, U8.7
SDA8: J41.3, J42.3, J43.2, J44.4, R42.1, U9.7
SDA_PU1: JP3.3, R1.2
SDA_PU2: JP15.3, R6.2
SDA_PU3: JP24.3, R12.2
SDA_PU4: JP33.3, R17.2
SDA_PU5: JP42.3, R22.2
SDA_PU6: JP51.3, R27.2
SDA_PU7: JP60.3, R32.2
SDA_PU8: JP69.3, R37.2
SDA_PU9: JP78.3, R42.2
STAT: R4.2, U4.10
STAT1: R8.2, U1.10
STAT2: R14.2, U2.10
STAT3: R19.2, U3.10
STAT4: R24.2, U5.10
STAT5: R29.2, U6.10
STAT6: R34.2, U7.10
STAT7: R39.2, U8.10
STAT8: R44.2, U9.10
SWITCH: S1.4, U4.5
SWITCH1: S2.4, U1.5
SWITCH2: S3.4, U2.5
SWITCH3: S4.4, U3.5
SWITCH4: S5.4, U5.5
SWITCH5: S6.4, U6.5
SWITCH6: S7.4, U7.5
SWITCH7: S8.4, U8.5
SWITCH8: S9.4, U9.5
~INT1: J10.1, R9.1, U1.13
~INT2: J15.1, R15.1, U2.13
~INT3: J20.1, R20.1, U3.13
~INT4: J25.1, R25.1, U5.13
~INT5: J30.1, R30.1, U6.13
~INT6: J35.1, R35.1, U7.13
~INT7: J40.1, R40.1, U8.13
~INT8: J45.1, R45.1, U9.13
~INT: J5.1, R11.1, U4.13
~RST1: J9.5, R7.1, U1.4
~RST2: J14.5, R13.1, U2.4
~RST3: J19.5, R18.1, U3.4
~RST4: J24.5, R23.1, U5.4
~RST5: J29.5, R28.1, U6.4
~RST6: J34.5, R33.1, U7.4
~RST7: J39.5, R38.1, U8.4
~RST8: J44.5, R43.1, U9.4
~RST: J7.5, R3.1, U4.4

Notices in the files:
parts and their libraries:
Released under the Creative Commons Attribution Share-Alike 4.0 License
https://creativecommons.org/licenses/by-sa/4.0
